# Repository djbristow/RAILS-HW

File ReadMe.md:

# RAILS-HW
&copy; David Bristow, 2020

# Version
* 1.1.1 - 4/18/2020

RAILS-HW contains the hardware designs specifically supporting the RAILS project.
For further information see http://kjcrr.org/rails

The hardware designs were developed using KiCad. For further information see https://www.kicad.org

## License

    The documentation in this repository is licensed under the TAPR Open Hardware License, Version 1.0 (the "License");
    you may not use this documentation except in compliance with the License.
    You may obtain a copy of the License at

       https://tapr.org/the-tapr-open-hardware-license/

    Unless required by applicable law or agreed to in writing, documentation
    distributed under the License is distributed on an "AS IS" BASIS,
    WITHOUT WARRANTIES OR CONDITIONS OF ANY KIND, either express or implied.
    See the License for the specific language governing permissions and
    limitations under the License.

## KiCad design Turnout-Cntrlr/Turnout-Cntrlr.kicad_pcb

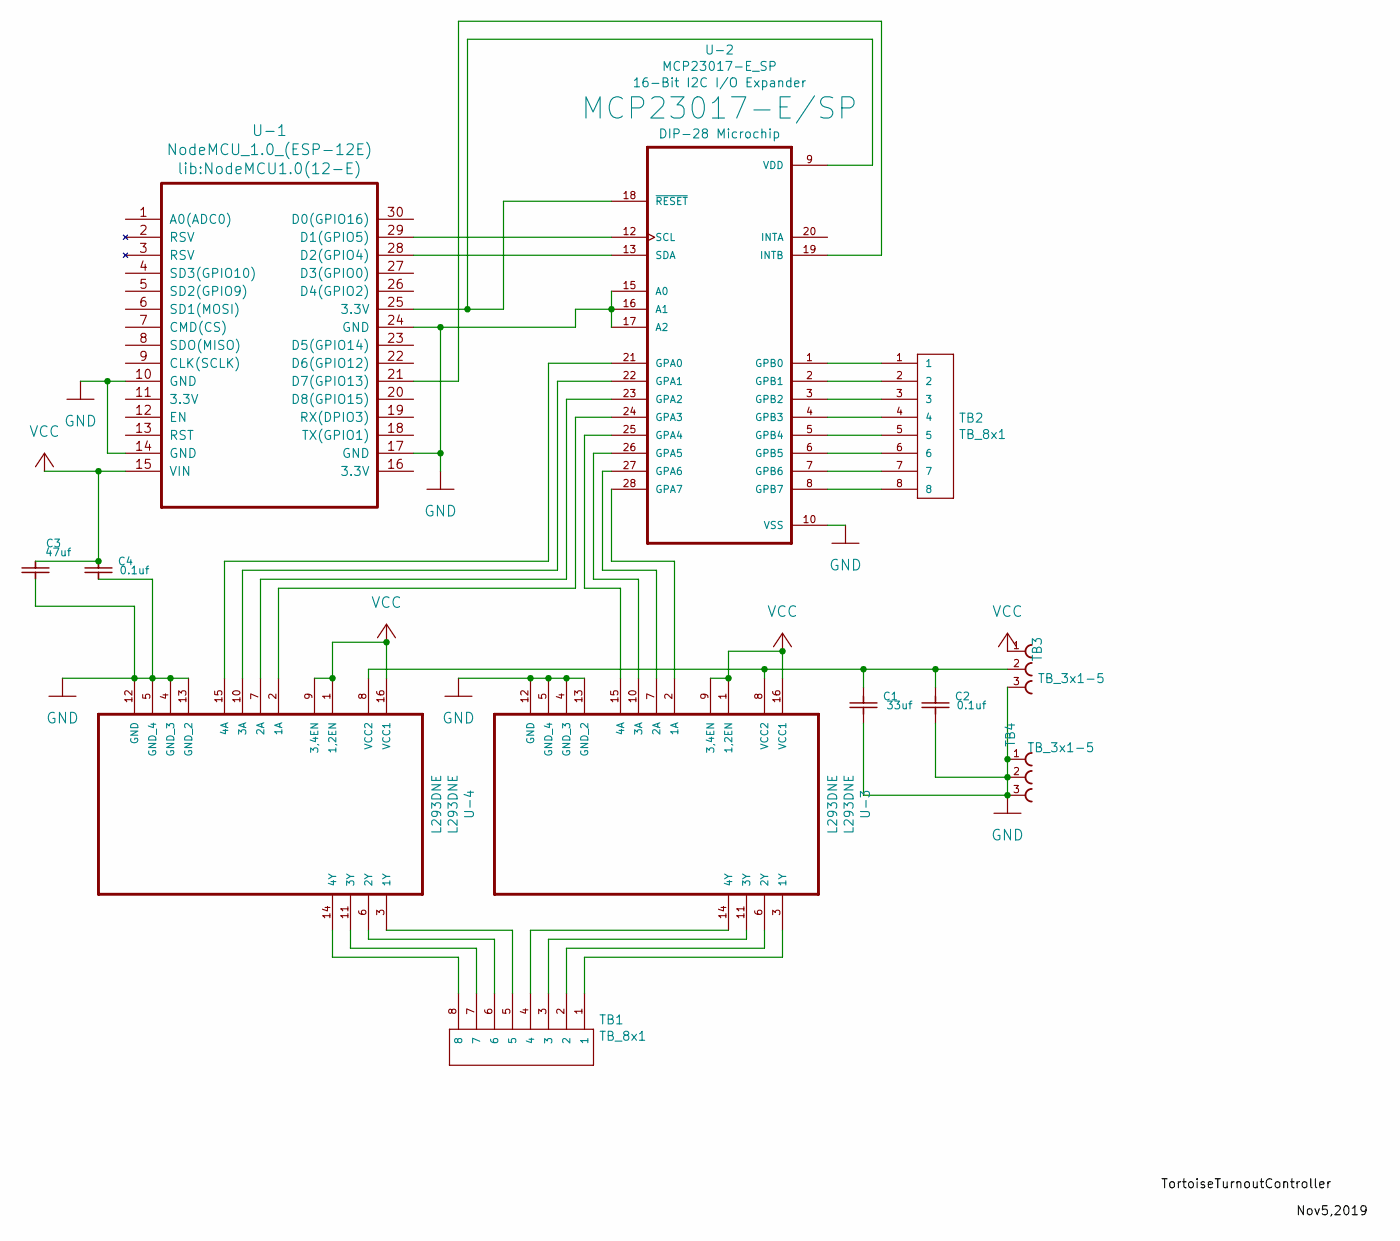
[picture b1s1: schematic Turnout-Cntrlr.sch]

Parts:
C1: 33uf; CAPPRD200W50D525H1250
C2, C4: 0.1uf; axial-cap
C3: 47uf; CAPPRD200W50D525H1250
TB1, TB2: TB_8x1; TB_8X1
TB3, TB4: TB_3x1-5; 691214110003
U-1: NodeMCU_1.0_(ESP-12E); NodeMCU1.0(12-E)
U-2: MCP23017-E_SP; DIP787W45P254L3556H508Q28
U-3, U-4: L293DNE; DIP254P762X508-16

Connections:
GND: C1.2, C1.~, C2.2, C2.~, C3.2, C3.~, C4.2, C4.~, TB3.3, TB4.1, TB4.2, TB4.3, U-1.10 (GND), U-1.14 (GND), U-1.17 (GND), U-1.24 (GND), U-2.10 (VSS), U-2.15 (A0), U-2.16 (A1), U-2.17 (A2), U-3.4 (GND_3), U-3.5 (GND_4), U-3.12 (GND), U-3.13 (GND_2), U-4.4 (GND_3), U-4.5 (GND_4), U-4.12 (GND), U-4.13 (GND_2)
unnamed: C1.1 (in), C2.1 (in), TB3.2, U-3.8 (VCC2), U-4.8 (VCC2)
unnamed: TB1.1, U-3.3 (1Y)
unnamed: TB1.2, U-3.6 (2Y)
unnamed: TB1.3, U-3.11 (3Y)
unnamed: TB1.4, U-3.14 (4Y)
unnamed: TB1.5, U-4.3 (1Y)
unnamed: TB1.6, U-4.6 (2Y)
unnamed: TB1.7, U-4.11 (3Y)
unnamed: TB1.8, U-4.14 (4Y)
unnamed: TB2.1, U-2.1 (GPB0)
unnamed: TB2.2, U-2.2 (GPB1)
unnamed: TB2.3, U-2.3 (GPB2)
unnamed: TB2.4, U-2.4 (GPB3)
unnamed: TB2.5, U-2.5 (GPB4)
unnamed: TB2.6, U-2.6 (GPB5)
unnamed: TB2.7, U-2.7 (GPB6)
unnamed: TB2.8, U-2.8 (GPB7)
unnamed: U-1.21 (D7(GPIO13)), U-2.19 (INTB)
unnamed: U-1.25 (3.3V), U-2.9 (VDD), U-2.18 (~RESET~)
unnamed: U-1.28 (D2(GPIO4)), U-2.13 (SDA)
unnamed: U-1.29 (D1(GPIO5)), U-2.12 (SCL)
unnamed: U-2.21 (GPA0), U-4.15 (4A)
unnamed: U-2.22 (GPA1), U-4.10 (3A)
unnamed: U-2.23 (GPA2), U-4.7 (2A)
unnamed: U-2.24 (GPA3), U-4.2 (1A)
unnamed: U-2.25 (GPA4), U-3.15 (4A)
unnamed: U-2.26 (GPA5), U-3.10 (3A)
unnamed: U-2.27 (GPA6), U-3.7 (2A)
unnamed: U-2.28 (GPA7), U-3.2 (1A)
VCC: C3.1 (in), C4.1 (in), TB3.1, U-1.15 (VIN), U-3.1 (1,2EN), U-3.9 (3,4EN), U-3.16 (VCC1), U-4.1 (1,2EN), U-4.9 (3,4EN), U-4.16 (VCC1)

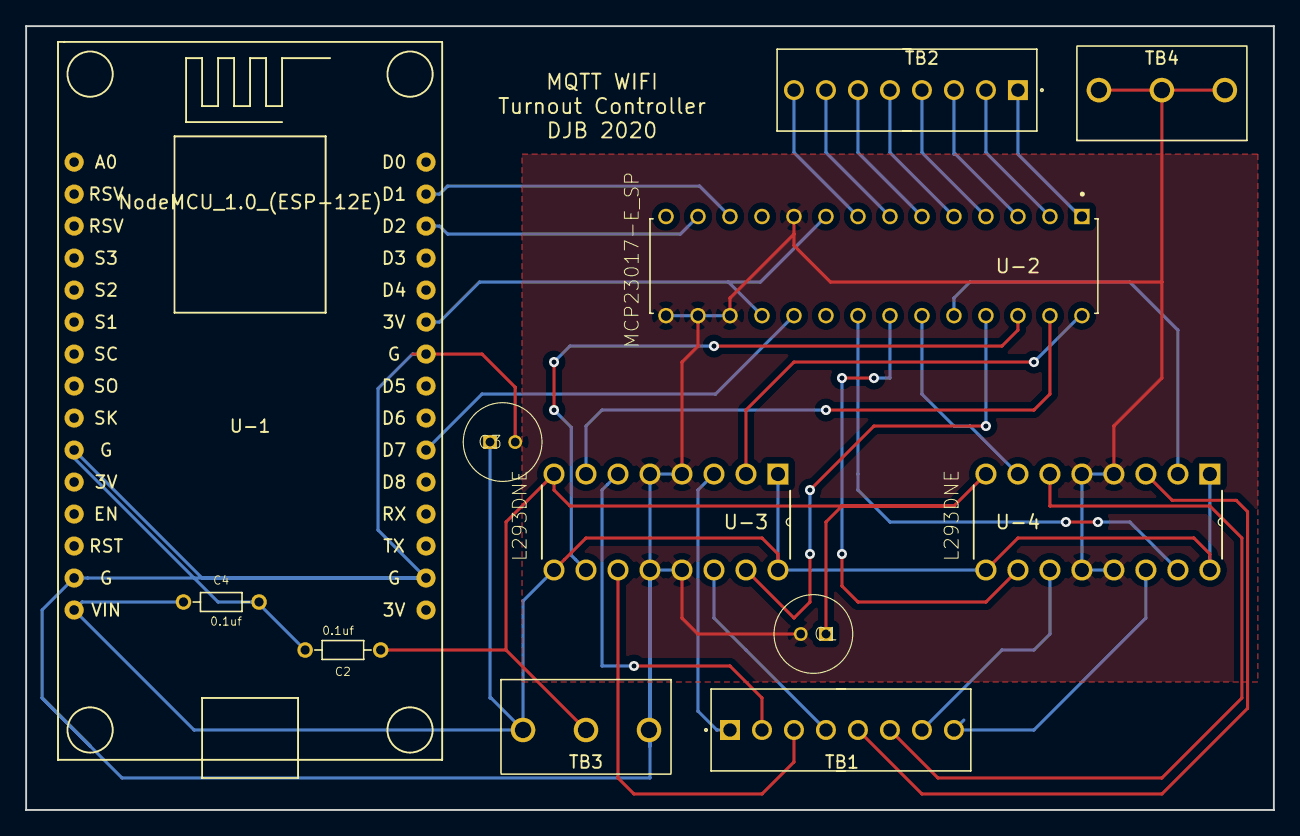
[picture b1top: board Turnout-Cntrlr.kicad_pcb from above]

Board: 2 copper layers, 99.1 x 62.2 mm, 12 parts (0 on the bottom side), 31 nets.

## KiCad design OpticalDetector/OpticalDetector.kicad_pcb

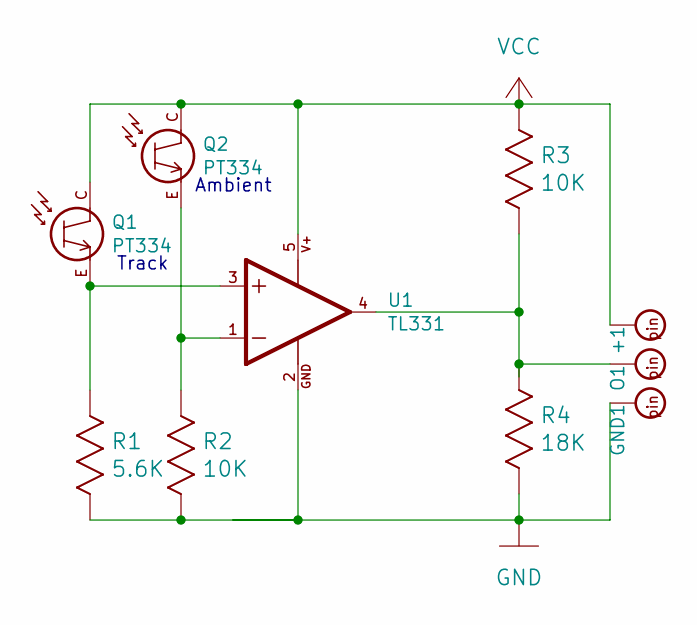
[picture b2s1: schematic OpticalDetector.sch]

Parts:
+1: PADS; SolderWirePad_1x01_Drill1mm
GND1: PADS; SolderWirePad_1x01_Drill1mm
O1: PADS; SolderWirePad_1x01_Drill1mm
Q1, Q2: PT334
R1: 5.6K; RES
R2, R3: 10K; RES
R4: 18K; RES
U1: TL331; SOT95P

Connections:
GND: GND1.1, R1.1, R2.1, R4.1, U1.2 (GND)
unnamed: O1.1, R3.1, R4.2, U1.4 (OUT)
unnamed: Q1.E, R1.2, U1.3 (+IN)
unnamed: Q2.E, R2.2, U1.1 (-IN)
VCC: +1.1, Q1.C, Q2.C, R3.2, U1.5 (VCC)

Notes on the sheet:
Ambient
Track

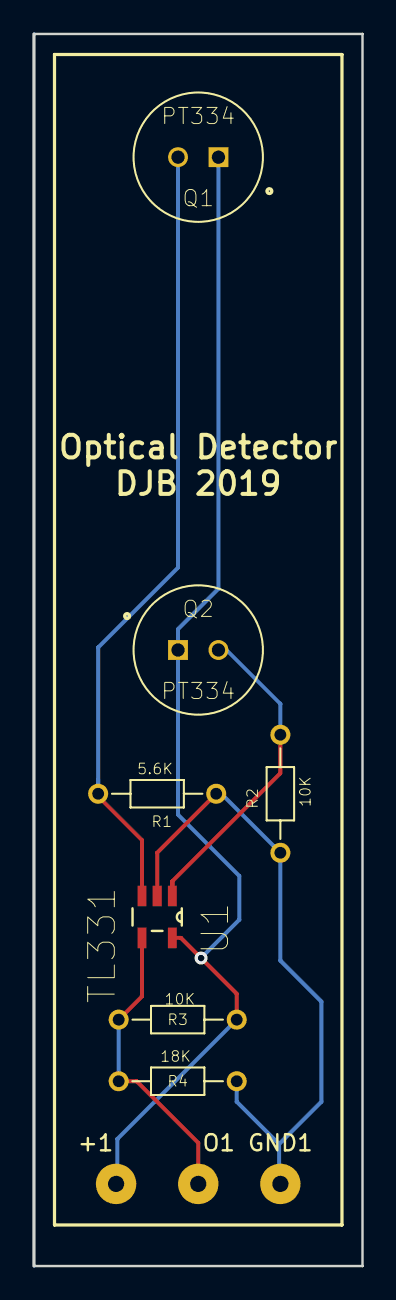
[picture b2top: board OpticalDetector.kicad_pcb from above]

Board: 2 copper layers, 20.3 x 76.2 mm, 10 parts (0 on the bottom side), 5 nets.

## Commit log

2020-04-18 added Optical detector and moved WiFi-RFID
2020-04-18 intial setup for the hardware projects
2020-04-18 added KiCad info
2020-04-20 changed license to be hardware specific
2020-05-13 initial relaese of Turnout Contrroller
2021-11-08 Update ReadMe.md
    https://forum.kicad.info/t/warning-avoid-all-links-to-kicad-pcb-org-use-kicad-org/31521
